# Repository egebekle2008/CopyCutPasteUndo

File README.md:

# Copy Cut Paste Undo
Copy Cut Paste Undo is a macropad made for making copying, cutting, pasting and undoing easier and faster by reducing the amount of keys you have to press.

# Specs
### BOM:

4x Cherry MX Switches\
1x XIAO RP2040\
4x Blank DSA Keycaps\
4x M3x16 Bolt\
4x M3 Heatset

### Others:
KMK Firmware\
Top Case.stl\
Bottom Case.stl

# Schematic

# PCB

# Case

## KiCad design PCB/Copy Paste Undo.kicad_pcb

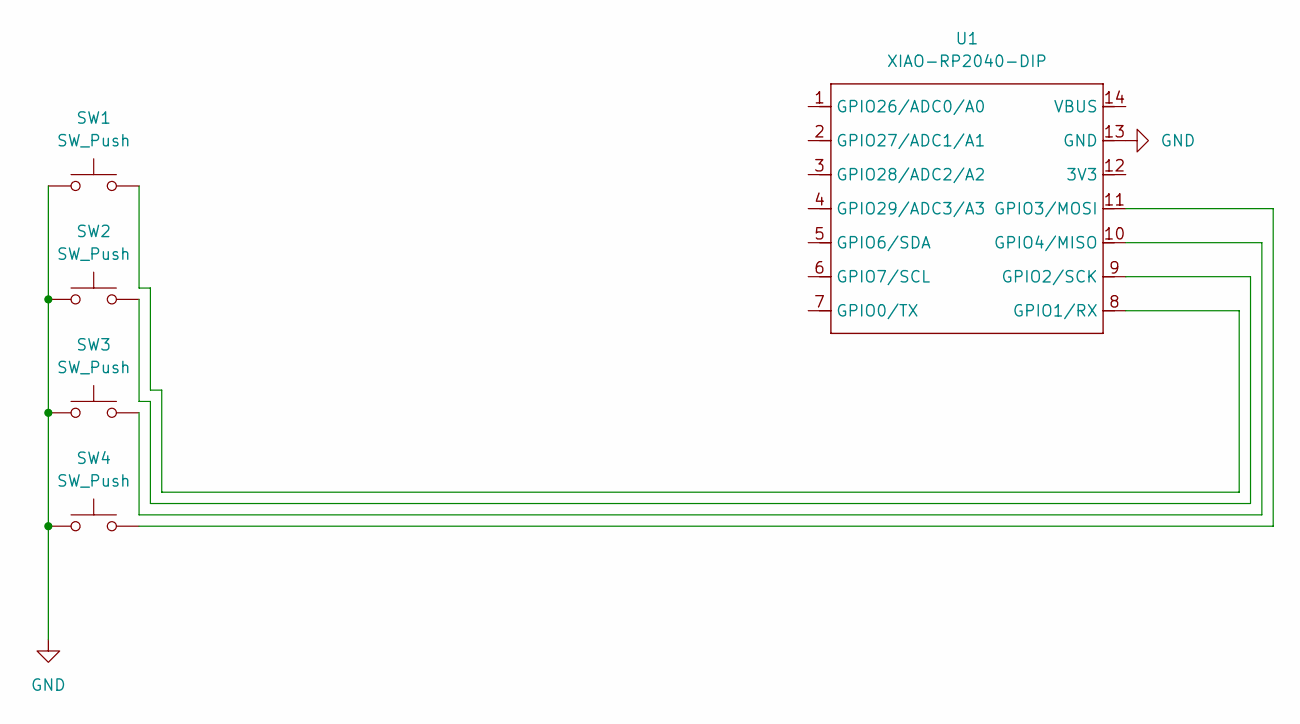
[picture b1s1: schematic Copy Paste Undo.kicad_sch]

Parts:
SW1, SW2, SW3, SW4: SW_Push; SW_Cherry_MX_1.00u_PCB
U1: XIAO-RP2040-DIP

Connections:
GND: SW1.1, SW2.1, SW3.1, SW4.1, U1.13 (GND)
unnamed: SW1.2, U1.8 (GPIO1/RX)
unnamed: SW2.2, U1.9 (GPIO2/SCK)
unnamed: SW4.2, U1.11 (GPIO3/MOSI)
unnamed: SW3.2, U1.10 (GPIO4/MISO)

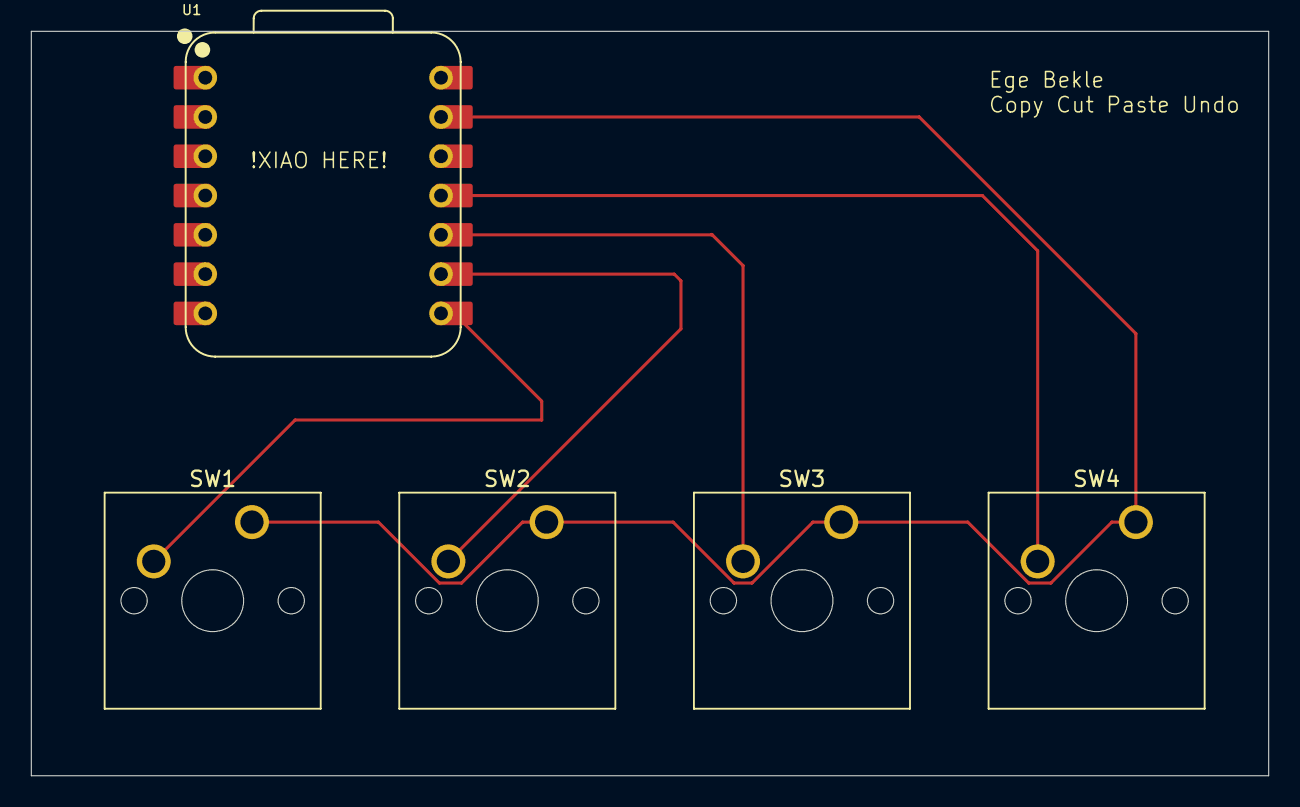
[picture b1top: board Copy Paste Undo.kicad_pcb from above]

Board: 2 copper layers, 80.0 x 48.1 mm, 5 parts (0 on the bottom side), 5 nets.

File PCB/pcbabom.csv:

"Id";"Designator";"Footprint";"Quantity";"Designation";"Supplier and ref";
1;"SW2,SW3,SW4,SW1";"SW_Cherry_MX_1.00u_PCB";4;"SW_Push";;;
2;"U1";"XIAO-RP2040-DIP";1;"XIAO-RP2040-DIP";;;

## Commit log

2026-01-06 Upload local files to github
2026-01-06 replaced the image in the readme with a fully assembled render
    title
2026-01-06 replaced stls with step files
